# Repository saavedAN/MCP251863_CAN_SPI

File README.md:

# MCP251863_CAN_SPI
PCB design and schematic for the MCP251863T-H/SS using SPI into CAN

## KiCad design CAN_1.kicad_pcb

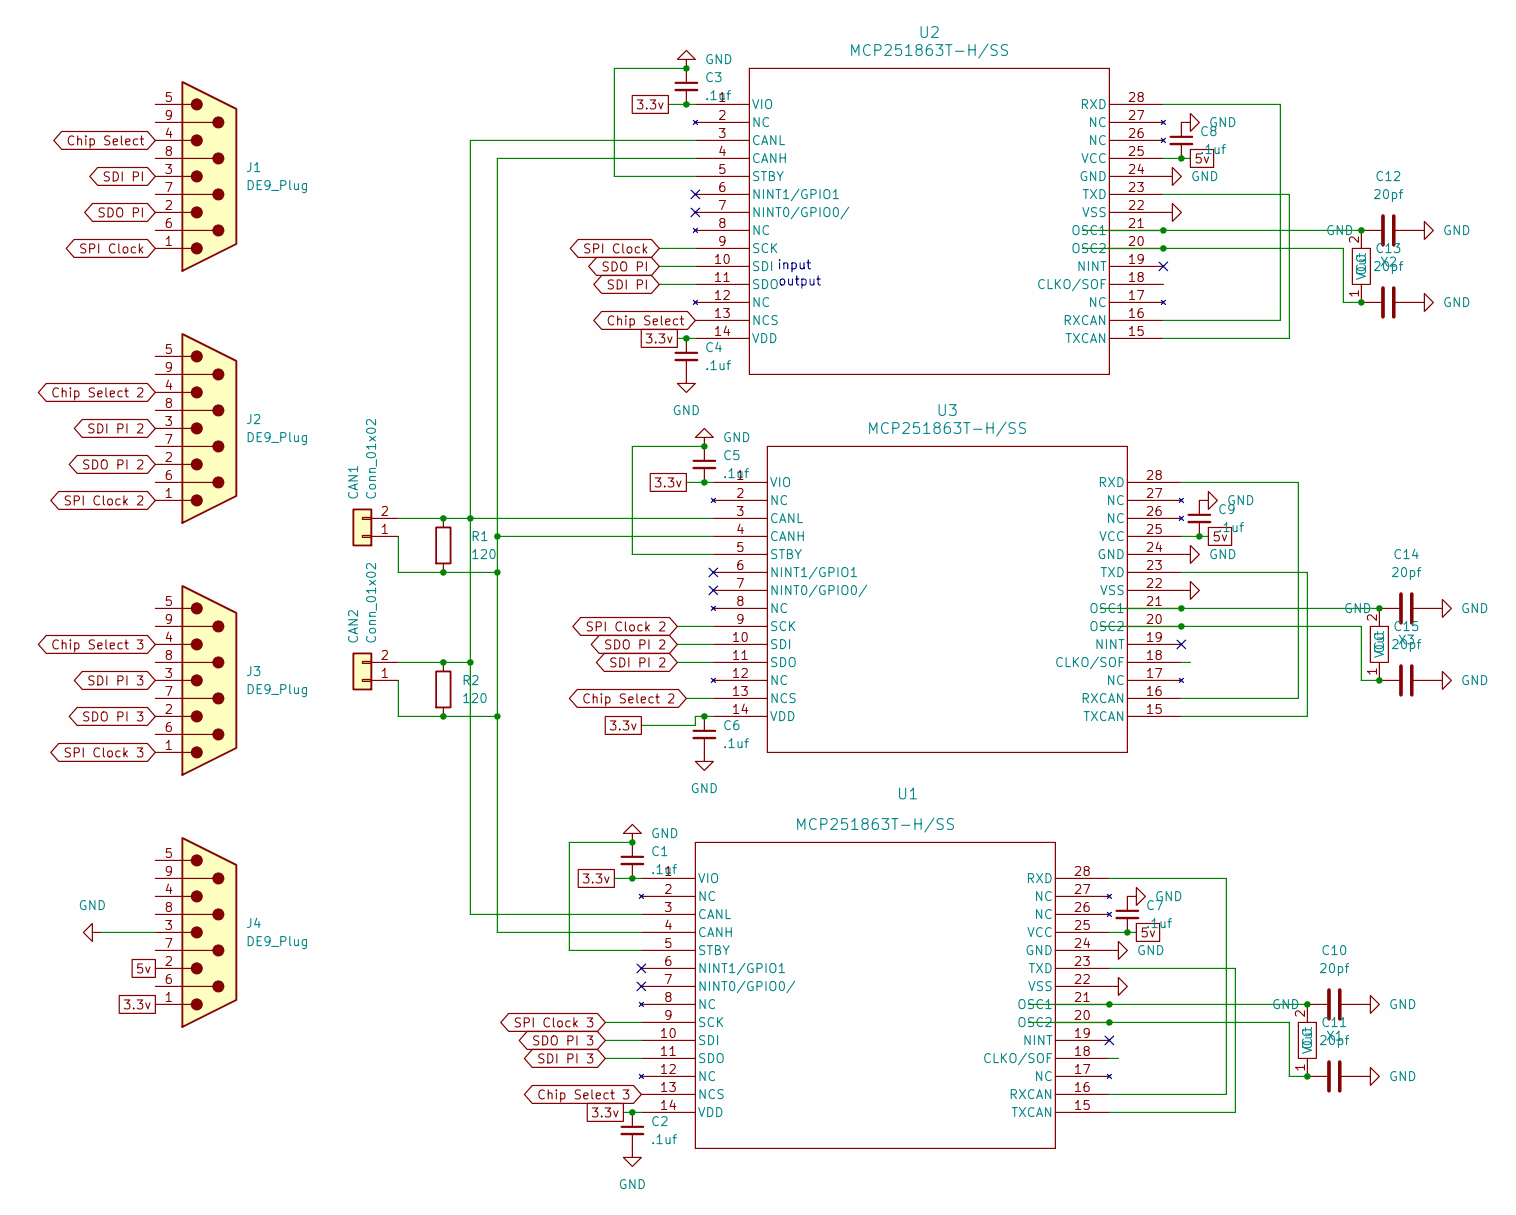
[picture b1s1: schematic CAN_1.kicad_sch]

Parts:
C1, C2, C3, C4, C5, C6, C7, C8, C9: .1uf; C_1206_3216Metric_Pad1.33x1.80mm_HandSolder
C10, C11, C12, C13, C14, C15: 20pf; C_1206_3216Metric_Pad1.33x1.80mm_HandSolder
CAN1, CAN2: Conn_01x02; JST_EH_B2B-EH-A_1x02_P2.50mm_Vertical
J1, J2, J3, J4: DE9_Plug; CONN_64TXLF_AMP
R1, R2: 120; R_Axial_DIN0207_L6.3mm_D2.5mm_P2.54mm_Vertical
U1, U2, U3: MCP251863T-H/SS; 28L-SSOP_MCH
X1, X2, X3: FC4STCBMF20.0

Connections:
3.3v: C1.2, C2.1, C3.2, C4.1, C5.2, C6.1, J4.1, U1.1 (VIO), U1.14 (VDD), U2.1 (VIO), U2.14 (VDD), U3.1 (VIO), U3.14 (VDD)
5v: C7.2, C8.2, C9.2, J4.2, U1.25 (VCC), U2.25 (VCC), U3.25 (VCC)
Chip Select: J1.4, U2.13 (NCS)
Chip Select 2: J2.4, U3.13 (NCS)
Chip Select 3: J3.4, U1.13 (NCS)
GND: C1.1, C2.2, C3.1, C4.2, C5.1, C6.2, C7.1, C8.1, C9.1, C10.2, C11.2, C12.2, C13.2, C14.2, C15.2, J4.3, U1.5 (STBY), U1.22 (VSS), U1.24 (GND), U2.5 (STBY), U2.22 (VSS), U2.24 (GND), U3.5 (STBY), U3.22 (VSS), U3.24 (GND)
unnamed: CAN1.1, CAN2.1, R1.2, R2.2, U1.4 (CANH), U2.4 (CANH), U3.4 (CANH)
unnamed: CAN1.2, CAN2.2, R1.1, R2.1, U1.3 (CANL), U2.3 (CANL), U3.3 (CANL)
unnamed: C10.1, U1.21 (OSC1), X1.2 (Out)
unnamed: C11.1, U1.20 (OSC2), X1.1 (VCC)
unnamed: U1.16 (RXCAN), U1.28 (RXD)
unnamed: U1.15 (TXCAN), U1.23 (TXD)
unnamed: C12.1, U2.21 (OSC1), X2.2 (Out)
unnamed: C13.1, U2.20 (OSC2), X2.1 (VCC)
unnamed: U2.16 (RXCAN), U2.28 (RXD)
unnamed: U2.15 (TXCAN), U2.23 (TXD)
unnamed: C14.1, U3.21 (OSC1), X3.2 (Out)
unnamed: C15.1, U3.20 (OSC2), X3.1 (VCC)
unnamed: U3.16 (RXCAN), U3.28 (RXD)
unnamed: U3.15 (TXCAN), U3.23 (TXD)
SDI PI: J1.3, U2.11 (SDO)
SDI PI 2: J2.3, U3.11 (SDO)
SDI PI 3: J3.3, U1.11 (SDO)
SDO PI: J1.2, U2.10 (SDI)
SDO PI 2: J2.2, U3.10 (SDI)
SDO PI 3: J3.2, U1.10 (SDI)
SPI Clock: J1.1, U2.9 (SCK)
SPI Clock 2: J2.1, U3.9 (SCK)
SPI Clock 3: J3.1, U1.9 (SCK)

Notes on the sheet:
input
output

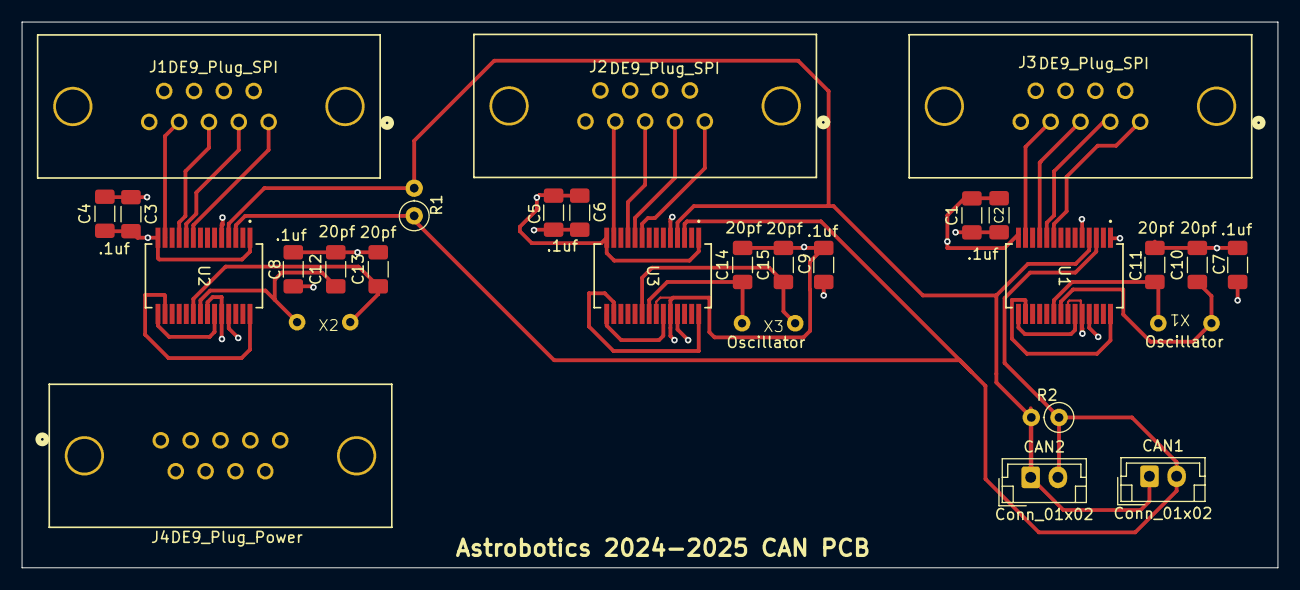
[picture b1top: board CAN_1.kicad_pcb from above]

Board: 4 copper layers, 115.3 x 50.1 mm, 29 parts (0 on the bottom side), 29 nets.

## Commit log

2025-01-02 Add files via upload
    Included are the footprint and schematic files for the MCP2515 CAN module. this will hopefully allow for integration of this module in a larger-scale PCB and allow for modular use.
